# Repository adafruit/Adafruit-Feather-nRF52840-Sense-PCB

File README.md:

## Adafruit Feather nRF52840 Sense PCB

<a href="http://www.adafruit.com/products/4516"><br/>
Click here to purchase one from the Adafruit shop</a>

PCB files for the Adafruit Feather nRF52840 Sense. 

Format is EagleCAD schematic and board layout
* https://www.adafruit.com/product/4516

### Description

The Adafruit Feather Bluefruit Sense takes our popular Feather nRF52840 Express and adds a smorgasbord of sensors to make a great wireless sensor platform. This Feather microcontroller comes with Bluetooth Low Energy and native USB support featuring the nRF52840!  This Feather is an 'all-in-one' Arduino-compatible + Bluetooth Low Energy with built in USB plus battery charging. With native USB it works great with CircuitPython, too.

Like the Feather nRF52840, this chip comes with Arduino IDE support - you can program the nRF52840 chip directly to take full advantage of the Cortex-M4 processor, and then calling into the Nordic SoftDevice radio stack when you need to communicate over BLE. Since the underlying API and peripherals are the same for the '832 and '840, you can supercharge your older nRF52832 projects with the same exact code, with a single recompile!

This Feather is also a BLE-friendly CircuitPython board! CircuitPython works best with disk drive access, and this is the only BLE-plus-USB-native chip that has the memory to handle running a little Python interpreter. The massive RAM and speedy Cortex M4F chip make this a good match. Make centrals or peripherals with the ease of CircuitPython.

A chorus of supporting sensors surround the module so you can do all sorts of environmental and motion sensing:

* ST Micro series 9-DoF motion - LSM6DS33 Accel/Gyro + LIS3MDL magnetometer
* APDS9960 Proximity, Light, Color, and Gesture Sensor
* PDM Microphone sound sensor
* SHT Humidity
* BMP280 temperature and barometric pressure/altitude

Features:

* ARM Cortex M4F (with HW floating point acceleration) running at 64MHz
* 1MB flash and 256KB SRAM
* Native Open Source USB stack - pre-programmed with UF2 bootloader
* Bluetooth Low Energy compatible 2.4GHz radio (Details available in the nRF52840 product specification)
* FCC / IC / TELEC certified module
* Up to +8dBm output power
* 21 GPIO, 6 x 12-bit ADC pins, up to 12 PWM outputs (3 PWM modules with 4 outputs each)
* Pin #13 red LED for general purpose blinking, Blue LED for general purpose connection status, NeoPixel for colorful feedback
* Power/enable pin
* Measures 2.0" x 0.9" x 0.28" (51mm x 23mm x 7.2mm) without headers soldered in
* Light as a (large?) feather - 6 grams
* 4 mounting holes
* Reset button
* SWD debug pads on bottom of PCB
* Works out of the box with all of our Adafruit FeatherWings! (Even the UART-using ones like the GPS FeatherWing)

As of January 10, 2024 - We have replaced the discontinued LSM6DS33 with an LSM6DS3TR-C 6 DoF sensor. The performance is improved however new firmware libraries will need to be used in order to read the accelerometer and gyroscope.

### License

Adafruit invests time and resources providing this open source design, please support Adafruit and open-source hardware by purchasing products from [Adafruit](https://www.adafruit.com)!

Designed by Limor Fried/Ladyada for Adafruit Industries.

Creative Commons Attribution/Share-Alike, all text above must be included in any redistribution. 
See license.txt for additional details.

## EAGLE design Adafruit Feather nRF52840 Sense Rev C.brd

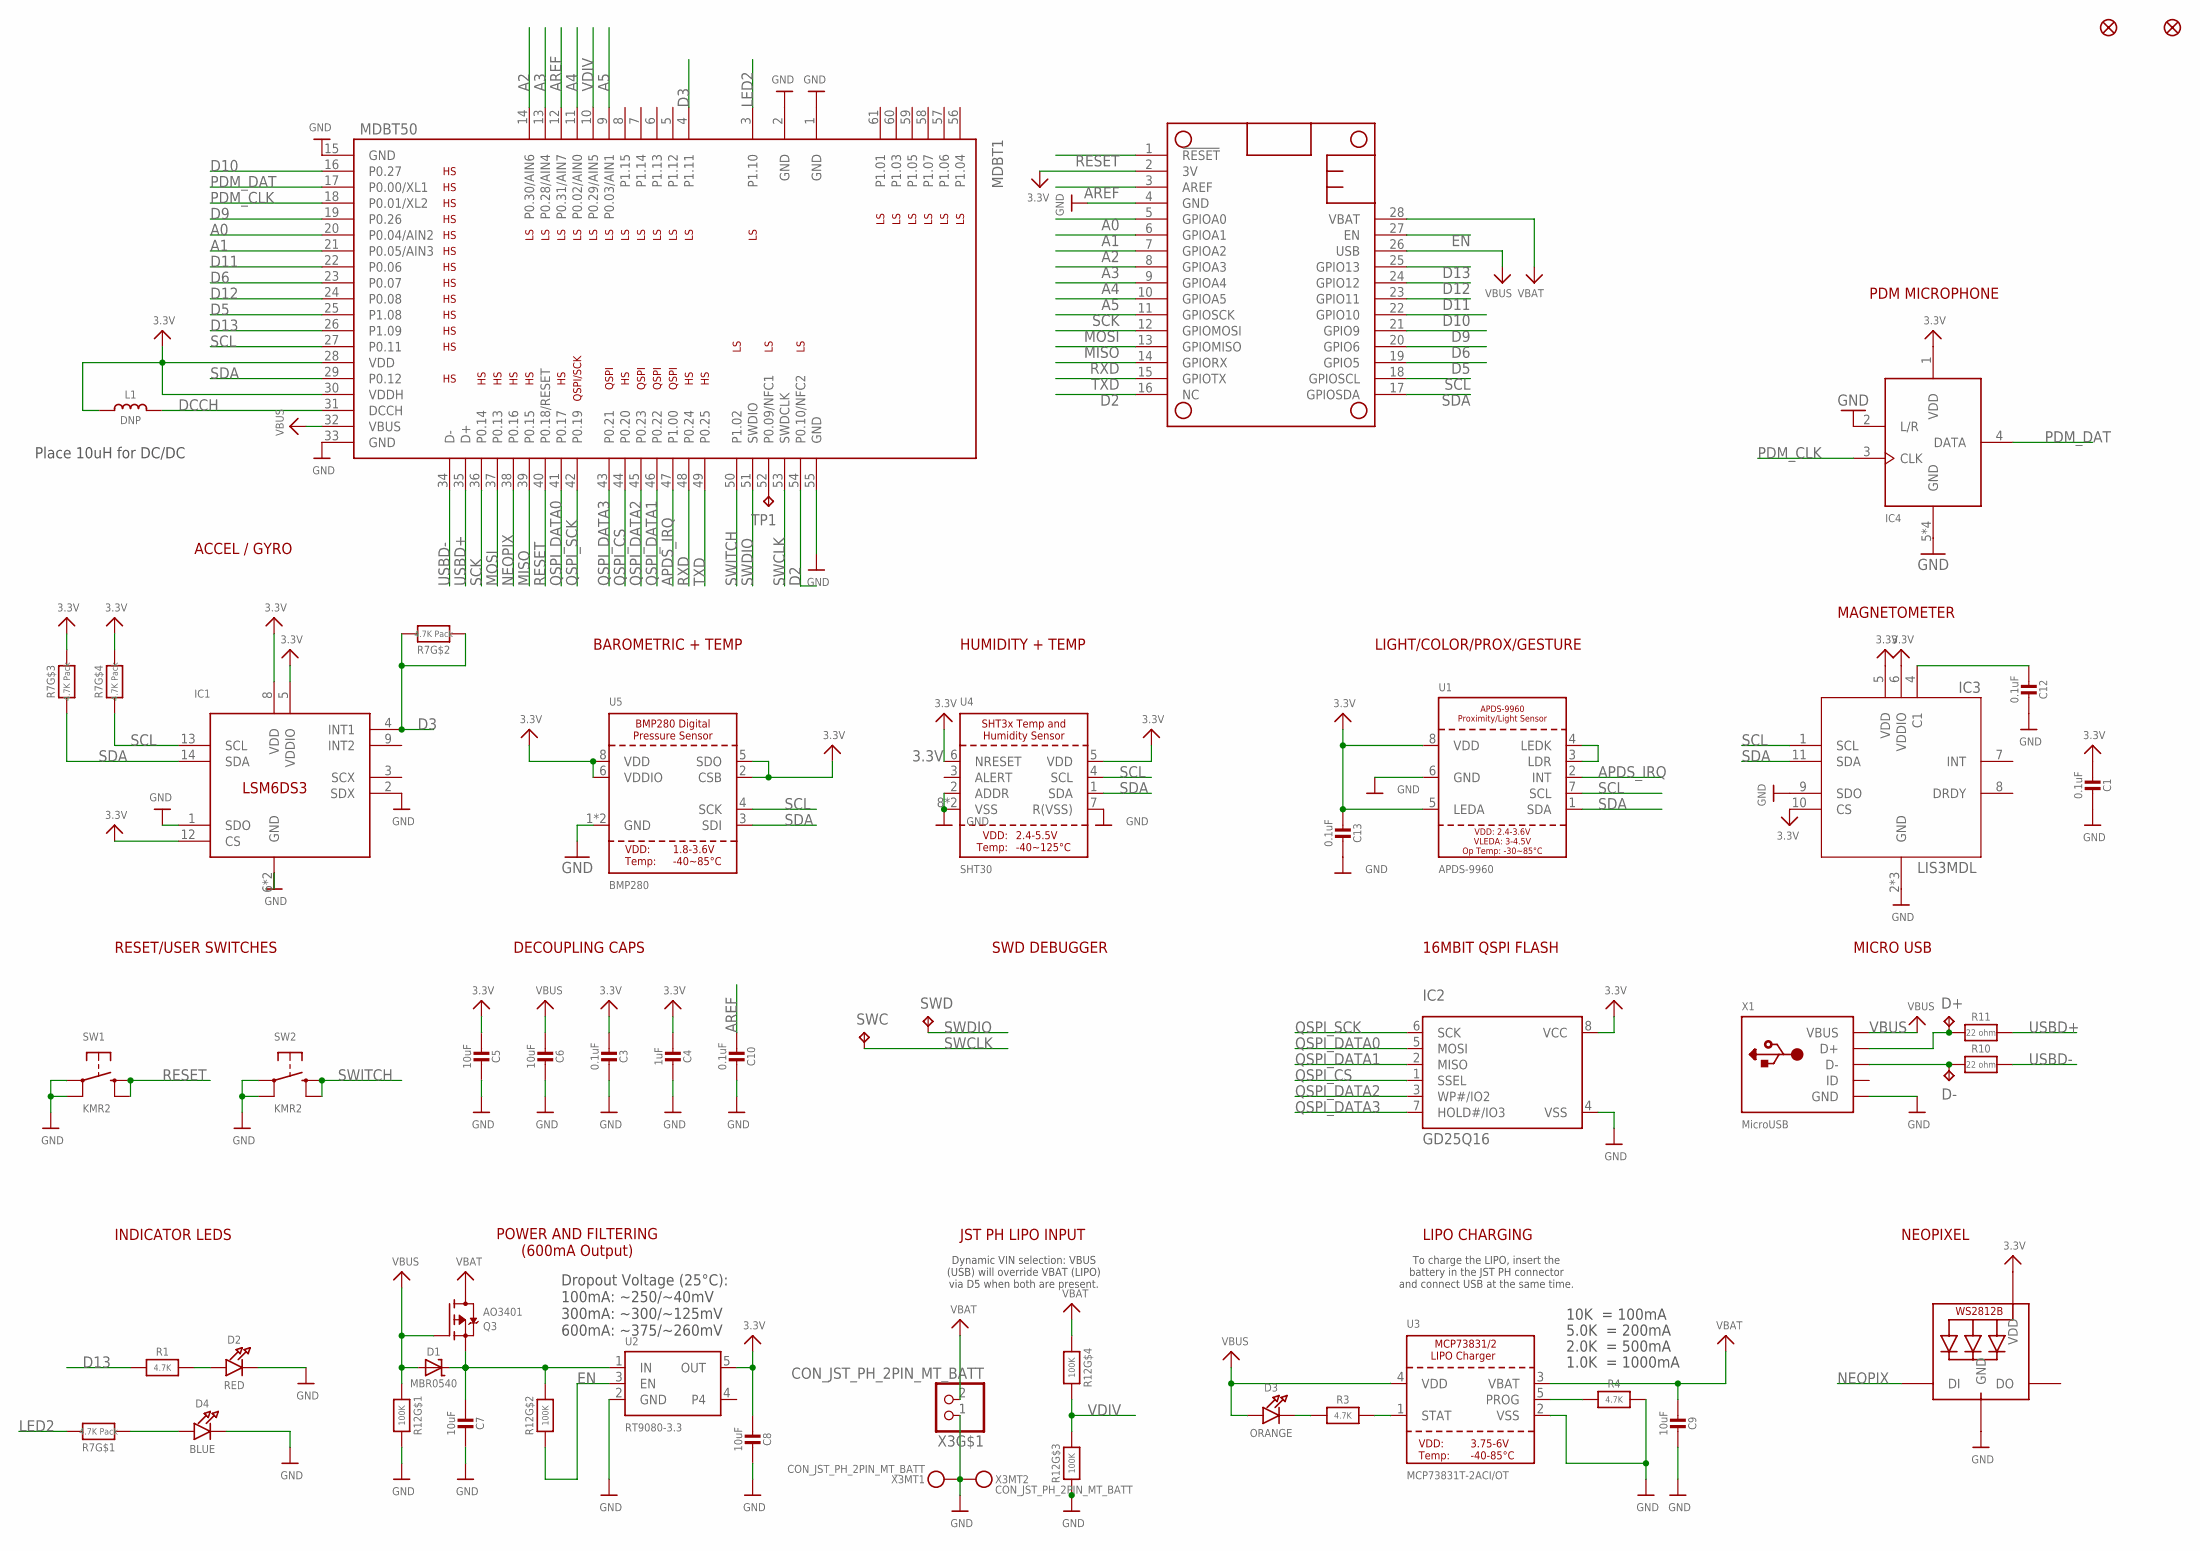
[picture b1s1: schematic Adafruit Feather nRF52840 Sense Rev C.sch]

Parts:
C1, C3, C10, C12, C13: 0.1uF; 0603-NO
C4: 1uF; 0603-NO
C5, C6, C7, C8, C9: 10uF; 0805-NO
D1: MBR0540; SOD-123
D2: RED; CHIPLED_0603_NOOUTLINE
D3: ORANGE; CHIPLED_0603_NOOUTLINE
D4: BLUE; CHIPLED_0603_NOOUTLINE
D+: TPTP10R; TP10R
D-: TPTP10R; TP10R
FID1, FID2: FIDUCIAL_1MM
IC1: LSM6DS3; LGA-14L
IC2: GD25Q16; USON8
IC3: LIS3MDL; LGA12_2X2MM
IC4: MIC_PDM; SPK0415HM4H
L1: DNP; _0805MP
LED1: WS2812B_3535FULL; LED3535_FULLPADS
MDBT1: MDBT50
MS1: FEATHERWING_NODIM
Q3: AO3401; SOT23-R
R1, R3, R4: 4.7K; 0603-NO
R7: 4.7K Pack; RESPACK_4X0603
R10, R11: 22 ohm; 0603-NO
R12: 100K; RESPACK_4X0603
SW1, SW2: KMR2; BTN_RKB2_4.6X2.8
SWC: TPTP12R; TP12R
SWD: TPTP12R; TP12R
TP1: TPTP10R; TP10R
U1: APDS-9960
U2: RT9080-3.3; SOT23-5; JLC_ROTATION 0
U3: MCP73831T-2ACI/OT; SOT23-5
U4: SHT30; SHT3X
U5: BMP280
X1: MicroUSB; 4UCONN_20329_V2
X3: CON_JST_PH_2PIN_MT_BATT; JSTPH2_BATT

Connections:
3.3V: C1.2, C3.2, C4.2, C5.2, C8.2, C13.2, IC1.5 (VDDIO), IC1.8 (VDD), IC1.12 (CS), IC2.8 (VCC), IC3.5 (VDD), IC3.6 (VDDIO), IC3.10 (CS), IC4.1 (VDD), L1.1, LED1.2 (VDD), MDBT1.28 (VDD), MDBT1.30 (VDDH), MS1.2 (3V), R7.5 (2), R7.6 (2), U1.5 (LEDA), U1.8 (VDD), U2.5 (OUT), U4.5 (VDD), U4.6 (NRESET), U5.2 (CSB), U5.5 (SDO), U5.6 (VDDIO), U5.8 (VDD)
A0: MDBT1.20 (P0.04/AIN2), MS1.5 (GPIOA0)
A1: MDBT1.21 (P0.05/AIN3), MS1.6 (GPIOA1)
A2: MDBT1.14 (P0.30/AIN6), MS1.7 (GPIOA2)
A3: MDBT1.13 (P0.28/AIN4), MS1.8 (GPIOA3)
A4: MDBT1.11 (P0.02/AIN0), MS1.9 (GPIOA4)
A5: MDBT1.9 (P0.03/AIN1), MS1.10 (GPIOA5)
APDS_IRQ: MDBT1.47 (P1.00), U1.2 (INT)
AREF: C10.2, MDBT1.12 (P0.31/AIN7), MS1.3 (AREF)
CAP1: C12.2, IC3.4 (C1)
D2: MDBT1.54 (P0.10/NFC2), MS1.16 (NC)
D3: IC1.4 (INT1), MDBT1.4 (P1.11), R7.2 (1), R7.7 (2)
D5: MDBT1.25 (P1.08), MS1.19 (GPIO5)
D6: MDBT1.23 (P0.07), MS1.20 (GPIO6)
D9: MDBT1.19 (P0.26), MS1.21 (GPIO9)
D10: MDBT1.16 (P0.27), MS1.22 (GPIO10)
D11: MDBT1.22 (P0.06), MS1.23 (GPIO11)
D12: MDBT1.24 (P0.08), MS1.24 (GPIO12)
D13: MDBT1.26 (P1.09), MS1.25 (GPIO13), R1.1
D+: D+.TP, R11.1, X1.D+
D-: D-.TP, R10.1, X1.D-
DCCH: L1.2, MDBT1.31 (DCCH)
EN: MS1.27 (EN), R12.2 (1), U2.3 (EN)
GND: C1.1, C3.1, C4.1, C5.1, C6.1, C7.1, C8.1, C9.1, C10.1, C12.1, C13.1, D2.C, D4.C, IC1.1 (SDO), IC1.2 (SDX), IC1.6 (GND), IC1.7 (GND), IC2.4 (VSS), IC3.2 (GND), IC3.3 (GND), IC3.9 (SDO), IC3.12 (GND), IC4.2 (L/R), IC4.5 (GND), IC4.6 (GND), IC4.7 (GND), IC4.8 (GND), LED1.4 (GND), MDBT1.1 (GND), MDBT1.2 (GND), MDBT1.15 (GND), MDBT1.33 (GND), MDBT1.55 (GND), MS1.4 (GND), R4.2, R12.3 (1), R12.8 (2), SW1.A, SW1.A' (P1), SW2.A, SW2.A' (P1), U1.6 (GND), U2.2 (GND), U3.2 (VSS), U4.2 (ADDR), U4.7 (R(VSS)), U4.8 (VSS), U4.THERMAL (VSS), U5.1 (GND), U5.7 (GND), X1.BASE@1 (GND), X1.BASE@2 (GND), X1.GND, X1.SPRT@1 (GND), X1.SPRT@2 (GND), X1.SPRT@3 (GND), X1.SPRT@4 (GND), X3.1, X3.NC1, X3.NC2
LED2: MDBT1.3 (P1.10), R7.8 (2)
MISO: MDBT1.39 (P0.15), MS1.13 (GPIOMISO)
MOSI: MDBT1.37 (P0.13), MS1.12 (GPIOMOSI)
unnamed: D3.C, R3.1
unnamed: U1.3 (LDR), U1.4 (LEDK)
unnamed: D4.A, R7.1
unnamed: D2.A, R1.2
unnamed: R3.2, U3.1 (STAT)
unnamed: R4.1, U3.5 (PROG)
NEOPIX: LED1.1 (DI), MDBT1.38 (P0.16)
NFC2: MDBT1.52 (P0.09/NFC1), TP1.TP
PDM_CLK: IC4.3 (CLK), MDBT1.18 (P0.01/XL2)
PDM_DAT: IC4.4 (DATA), MDBT1.17 (P0.00/XL1)
QSPI_CS: IC2.1 (SSEL), MDBT1.44 (P0.20)
QSPI_DATA0: IC2.5 (MOSI), MDBT1.41 (P0.17)
QSPI_DATA1: IC2.2 (MISO), MDBT1.46 (P0.22)
QSPI_DATA2: IC2.3 (WP#/IO2), MDBT1.45 (P0.23)
QSPI_DATA3: IC2.7 (HOLD#/IO3), MDBT1.43 (P0.21)
QSPI_SCK: IC2.6 (SCK), MDBT1.42 (P0.19)
RESET: MDBT1.40 (P0.18/RESET), MS1.1 (!RESET), SW1.B (S), SW1.B' (S1)
RXD: MDBT1.48 (P0.24), MS1.14 (GPIORX)
SCK: MDBT1.36 (P0.14), MS1.11 (GPIOSCK)
SCL: IC1.13 (SCL), IC3.1 (SCL), MDBT1.27 (P0.11), MS1.18 (GPIOSCL), R7.4 (1), U1.7 (SCL), U4.4 (SCL), U5.4 (SCK)
SDA: IC1.14 (SDA), IC3.11 (SDA), MDBT1.29 (P0.12), MS1.17 (GPIOSDA), R7.3 (1), U1.1 (SDA), U4.1 (SDA), U5.3 (SDI)
SWCLK: MDBT1.53 (SWDCLK), SWC.TP
SWDIO: MDBT1.51 (SWDIO), SWD.TP
SWITCH: MDBT1.50 (P1.02), SW2.B (S), SW2.B' (S1)
TXD: MDBT1.49 (P0.25), MS1.15 (GPIOTX)
USBD+: MDBT1.35 (D+), R11.2
USBD-: MDBT1.34 (D-), R10.2
VBAT: C9.2, MS1.28 (VBAT), Q3.3 (D), R12.4 (1), U3.3 (VBAT), X3.2
VBUS: C6.2, D1.A, D3.A, MDBT1.32 (VBUS), MS1.26 (USB), Q3.1 (G), R12.1, U3.4 (VDD), X1.VBUS
VDIV: MDBT1.10 (P0.29/AIN5), R12.5 (2), R12.6 (2)
VHI: C7.2, D1.C, Q3.2 (S), R12.7 (2), U2.1 (IN)

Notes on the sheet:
10K = 100mA
5.0K = 200mA
2.0K = 500mA
1.0K = 1000mA
LIPO CHARGING
To charge the LIPO, insert the battery in the JST PH connector and connect USB at the same time.
POWER AND FILTERING (600mA Output)
JST PH LIPO INPUT
Dynamic VIN selection: VBUS (USB) will override VBAT (LIPO) via D5 when both are present.
Dropout Voltage (25°C): 100mA: ~250/~40mV 300mA: ~300/~125mV 600mA: ~375/~260mV
INDICATOR LEDS
RESET/USER SWITCHES
DECOUPLING CAPS
SWD DEBUGGER
16MBIT QSPI FLASH
MICRO USB
NEOPIXEL
Place 10uH for DC/DC
ACCEL / GYRO
BAROMETRIC + TEMP
HUMIDITY + TEMP
LIGHT/COLOR/PROX/GESTURE
MAGNETOMETER
PDM MICROPHONE

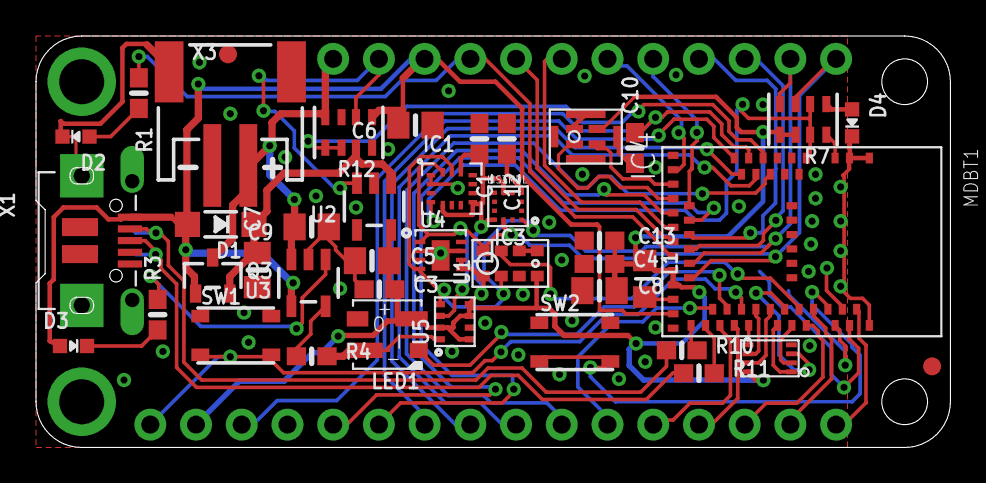
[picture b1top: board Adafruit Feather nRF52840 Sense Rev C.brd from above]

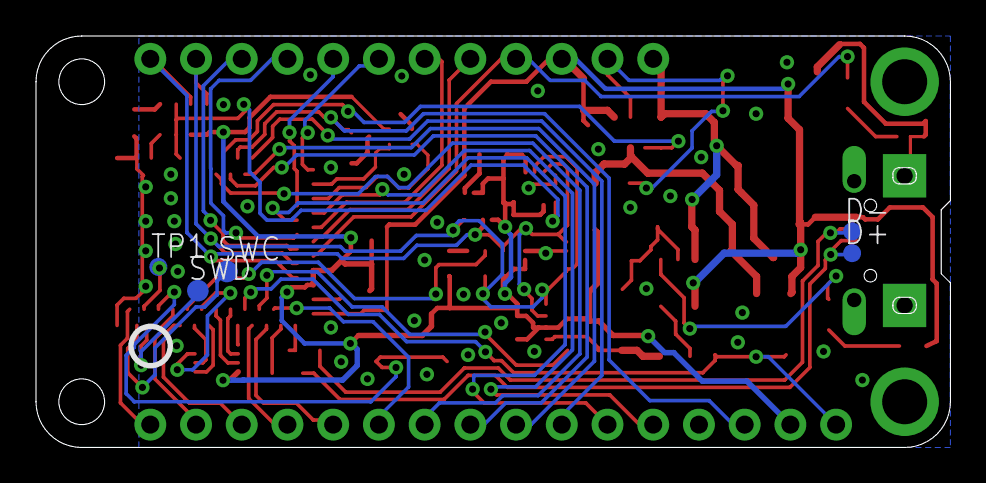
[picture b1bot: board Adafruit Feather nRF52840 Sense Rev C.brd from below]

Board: 2 copper layers, 50.8 x 22.9 mm, 50 parts (7 on the bottom side), 58 nets.

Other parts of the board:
U$10: PCBFEAT-REV-056
U$14: FEATHERSENSE_TOP
U$75: FEATHERSENSE_BOT

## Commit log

2020-03-11 Adding board files.
2021-05-15 Add pin reference PDF
2024-01-24 adding rev C

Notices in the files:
parts and their libraries:
microbuilder: This work is placed in the public domain, and may be freely used for commercial and non-commercial work with the following conditions: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
